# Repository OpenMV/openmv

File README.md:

# The Open-Source Machine Vision Project
  - [Overview](#overview)
  - [TensorFlow support](#tensorflow-support)
  - [Interface library](#interface-library)
    + [Note on serial port](#note-on-serial-port)
  - [ Building the firmware from source](#building-the-firmware-from-source)
  - [Contributing to the project](#contributing-to-the-project)
    + [Contribution guidelines](#contribution-guidelines)
    
## Overview

The OpenMV project brings machine vision to beginners with a user-friendly, open-source platform. OpenMV cameras are programmable in Python3 and feature advanced AI capabilities, including support for TensorFlow, ST Edge AI, and NPU acceleration through ARM Ethos-U55 and ST Neural-ART. The firmware includes a rich image image processing library, such as image filtering, feature detection, color tracking, QR and barcode decoding, AprilTag recognition, GIF and MJPEG recording and streaming, and much more.

The latest generation of OpenMV cameras includes the N6 and AE3 models. The OpenMV-N6 is powered by the STM32N6 microcontroller, which features a 1GHz/600 GOPS NPU, hardware H.264 encoding, high-speed USB, ISP, GPU, and a high-speed μSD card slot. It also comes equipped with WiFi/BLE, Gigabit Ethernet, and extensive GPIO pins—combining the power of a single-board computer with the flexibility of a microcontroller.

The OpenMV-AE3 is our smallest and most energy-efficient camera yet powered by the Alif Ensemble E3, with dual-core processors and dual Ethos-U55 NPUs. This ultra-low-power device can run YOLO models at 30 FPS while drawing only 0.25 W, and it consumes just 2.5 mW in deep sleep mode. It features a 1MP high-frame-rate color global shutter camera, an IMU, a microphone, an 8×8 distance sensor, and connectivity options such as high-speed USB, WiFi/BLE, and QWIIC—making it ideal for battery-powered AI vision applications.

Complementing the firmware is an intuitive, cross-platform IDE based on Qt Creator, specifically designed for machine vision development. The IDE lets users view the camera’s frame buffer in real time, adjust sensor settings, and run scripts directly on the device. It also provides a range of tools for image analysis, including tag generation, threshold definition, keypoint detection, and other processing functions.

The OpenMV project was successfully funded on Kickstarter in 2015 and has evolved significantly since its inception. For more information, visit [https://openmv.io](https://openmv.io).

## Interface library

The OpenMV Cam comes built-in with an RPC (Remote Python/Procedure Call) library which makes it easy to connect the OpenMV Cam to another microcontroller like the Arduino or ESP8266/32. The RPC Interface Library works over:

* Async Serial (UART) - at up **7.5 Mb/s** on the OpenMV Cam H7.
* I2C Bus - at up to **1 Mb/s** on the OpenMV Cam H7.
  * Using 1K pull up resistors.
* SPI Bus - at up to **20 Mb/s** on the OpenMV Cam H7.
  * Up to **80 Mb/s** or **40 Mb/s** is achievable with short enough wires.
* CAN Bus - at up to **1 Mb/s** on the OpenMV Cam H7.

With the RPC Library you can easily get image processing results, stream RAW or JPG image data, or have the OpenMV Cam control another Microcontroller for lower-level hardware control like driving motors.

You can find examples that run on the OpenMV Cam under `File->Examples->Remote Control` in OpenMV IDE and online [here](scripts/examples/34-Remote-Control). Finally, OpenMV provides the following libraries for interfacing your OpenMV Cam to other systems below:

* [Arduino Interface Library for CAN, I2C, SPI, UART Comms](https://github.com/openmv/openmv-arduino-rpc)
  * Works on all Arduino variants.
  * CAN support via the MCP2515 over SPI or via the CAN peripheral on the ESP32.

#### Note on serial port

If you only need to read `print()` output from a script running on an OpenMV camera over USB, then you only need to open the OpenMV camera Virtual COM Port and read lines of text from the serial port. For example (using [pyserial](https://pythonhosted.org/pyserial/index.html)):

```Python
import serial
ser = serial.Serial("COM3", timeout=1, dsrdtr=False)
while True:
    line = ser.readline().strip()
    if line: print(line)
```
The above code works for Windows, Mac, or Linux. You just need to change the above port name to the same name of the USB VCP port the OpenMV Cam shows up as (it will be under `/dev/` on Mac or Linux). Note that if you are opening the USB VCP port using another serial library and/or language make sure to set the DTR line to false - otherwise the OpenMV Cam will suppress printed output.

## Building the firmware from source

The easiest way to patch the firmware and rebuild it, is to fork this repository, enable Actions (from the Actions tab) in the forked repository, and pushing the changes. Our GitHub workflow rebuilds the firmware on pushes to the master branch and/or merging pull requests and generates a development release with attached separate firmware packages per supported board. For more complex changes, and building the OpenMV firmware from source locally, see [Building the Firmware From Source](https://github.com/openmv/openmv/blob/master/docs/firmware.md).

For more information about customizing your OpenMV Cam's configuration see [Board Configuration](docs/boards.md).

### Unix Port for Development

The Unix port runs OpenMV image processing without camera hardware. See the [Unix port guide](docs/unix-port.md) for the Linux Docker build, supported API and tests.

## Contributing to the project

Contributions are most welcome. If you are interested in contributing to the project, start by creating a fork of each of the following repositories:

* https://github.com/openmv/openmv.git
* https://github.com/openmv/micropython.git

Clone the forked openmv repository, and add a remote to the main openmv repository:
```bash
git clone --recursive https://github.com/<username>/openmv.git
git -C openmv remote add upstream https://github.com/openmv/openmv.git
```

Set the `origin` remote of the micropython submodule to the forked micropython repo:
```bash
git -C openmv/src/micropython remote set-url origin https://github.com/<username>/micropython.git
```

Finally add a remote to openmv's micropython fork:
```bash
git -C openmv/src/micropython remote add upstream https://github.com/openmv/micropython.git
```

Now the repositories are ready for pull requests. To send a pull request, create a new feature branch and push it to origin, and use Github to create the pull request from the forked repository to the upstream openmv/micropython repository. For example:
```bash
git checkout -b <some_branch_name>
<commit changes>
git push origin -u <some_branch_name>
```

### Contribution guidelines
Please follow the [best practices](https://developers.google.com/blockly/guides/modify/contribute/write_a_good_pr) when sending pull requests upstream. In general, the pull request should:
* Fix one problem. Don't try to tackle multiple issues at once.
* Split the changes into logical groups using git commits.
* Pull request title should be less than 78 characters, and match this pattern:
  * `<scope>:<1 space><description><.>`
* Commit subject line should be less than 78 characters, and match this pattern:
  * `<scope>:<1 space><description><.>`

Example PR titles or commit subject lines:
```
github: Update workflows.
Libtf: Add support for built-in models.
RPC library: Remove CAN bit timing function.
OPENMV4: Add readme template file.
ports/stm32/main.c: Fix storage label.
```

### Licensing

Most of the code in the repository is licensed under the MIT license, with the following exceptions:

* Some image library code is licensed under the GPL. This includes AGAST, LSD, and ZBAR. GPL code can be completely disabled in a build by defining `OMV_NO_GPL` in the `imlib_config.h` files.
* Third-party libraries and drivers in `lib` and `drivers` are licensed under various permissive licenses. Please consult the LICENSE file in each driver/library subdirectory for more details.
* Some drivers, modules, and libraries in OpenMV are proprietary and available for non-commercial use only. These proprietary components can be disabled during the build process. Official OpenMV hardware and licensed devices may use the proprietary code. For commercial licensing options, contact openmv@openmv.io.

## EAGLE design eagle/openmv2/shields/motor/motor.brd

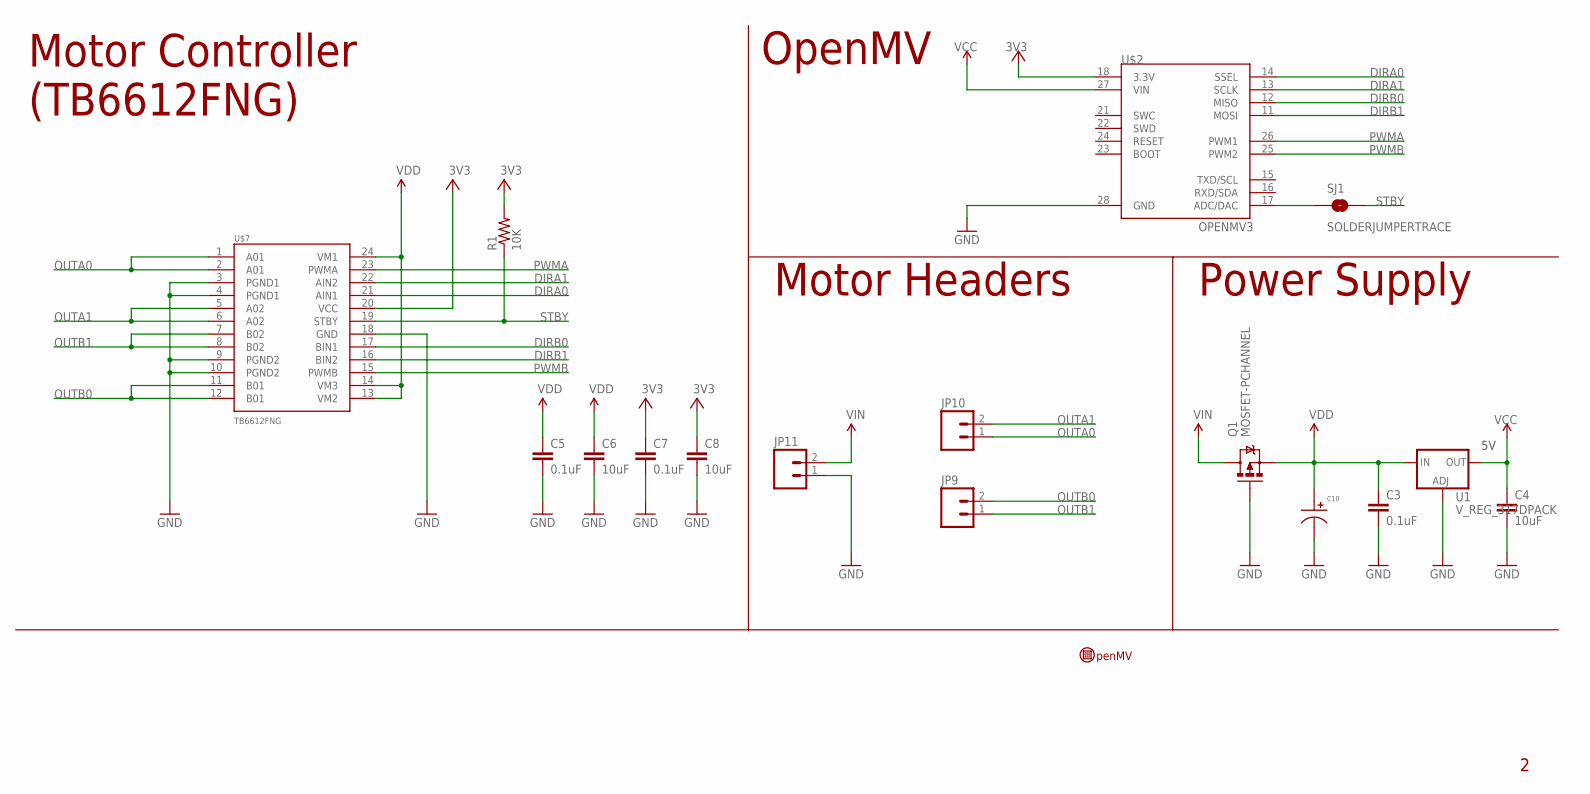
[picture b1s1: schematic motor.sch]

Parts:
C3, C5, C7: 0.1uF; 0603-CAP
C4, C6, C8: 10uF; 0805
C10: CAPACITOR_P_10MM; CP10MM
JP9, JP10, JP11: M023.5MM; SCREWTERMINAL-3.5MM-2
Q1: MOSFET-PCHANNEL; SOT23-3
R1: 10K; 0603-RES
SJ1: SOLDERJUMPERTRACE; SJ_2S-TRACE
U1: V_REG_317DPACK; V-REG_DPACK
U$2: OPENMV3
U$7: TB6612FNG; SSOP24
U$9: OPENMV-LOGO

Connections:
3V3: C7.1, C8.1, R1.2, U$2.18 (3.3V), U$7.20 (VCC)
DIRA0: U$2.14 (SSEL), U$7.21 (AIN1)
DIRA1: U$2.13 (SCLK), U$7.22 (AIN2)
DIRB0: U$2.12 (MISO), U$7.17 (BIN1)
DIRB1: U$2.11 (MOSI), U$7.16 (BIN2)
GND: C3.2, C4.2, C5.2, C6.2, C7.2, C8.2, C10.P$2, JP11.1, Q1.1 (G), U1.1 (ADJ), U$2.28 (GND), U$7.3 (PGND1), U$7.4 (PGND1), U$7.9 (PGND2), U$7.10 (PGND2), U$7.18 (GND)
OUTA0: JP10.1, U$7.1 (A01), U$7.2 (A01)
OUTA1: JP10.2, U$7.5 (A02), U$7.6 (A02)
OUTB0: JP9.2, U$7.11 (B01), U$7.12 (B01)
OUTB1: JP9.1, U$7.7 (B02), U$7.8 (B02)
PWMA: U$2.26 (PWM1), U$7.23 (PWMA)
PWMB: U$2.25 (PWM2), U$7.15 (PWMB)
STBY: R1.1, SJ1.2, U$7.19 (STBY)
STBY_TRACE: SJ1.1, U$2.17 (ADC/DAC)
VCC: C4.1, U1.4 (OUT), U$2.27 (VIN)
VDD: C3.1, C5.1, C6.1, C10.P$1, Q1.2 (S), U1.3 (IN), U$7.13 (VM2), U$7.14 (VM3), U$7.24 (VM1)
VIN: JP11.2, Q1.3 (D)

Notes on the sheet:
Motor Controller (TB6612FNG)
Motor Headers
OpenMV
Power Supply

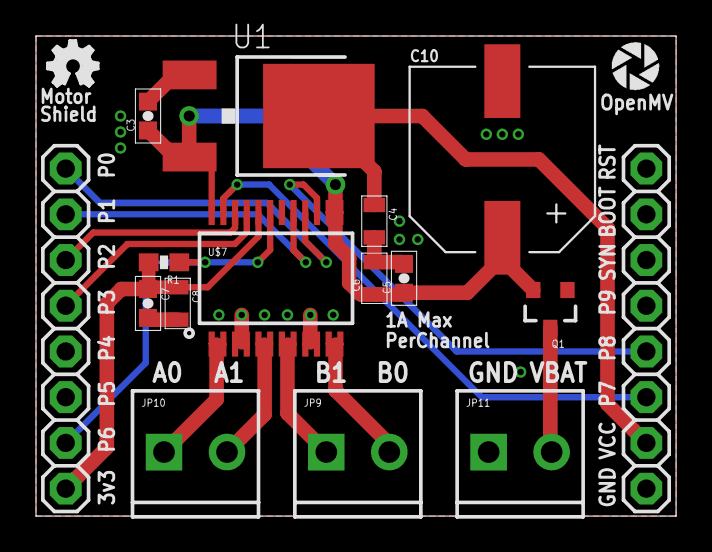
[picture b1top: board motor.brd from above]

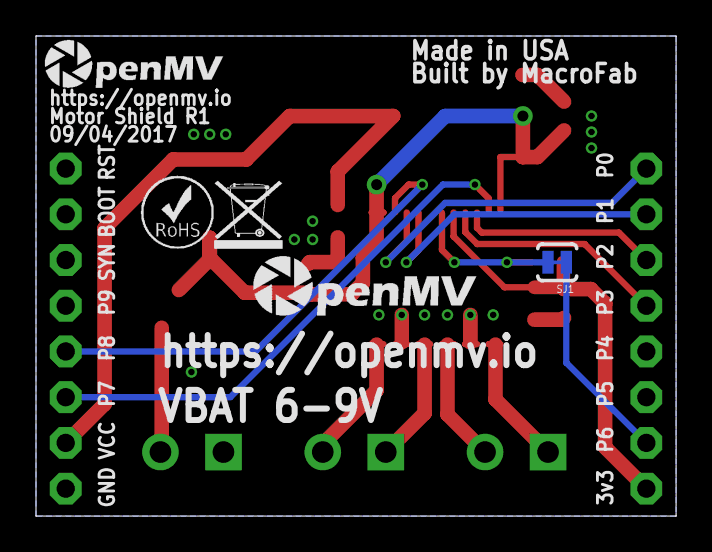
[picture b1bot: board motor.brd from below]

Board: 2 copper layers, 35.6 x 26.7 mm, 22 parts (5 on the bottom side), 17 nets.

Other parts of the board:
U$3: OMV-LOGO
U$5: ROHS
U$6: WEEE
U$10: OMV-LOGO-SMALL
U$11: OSHW_FILLX100_NOTEXT

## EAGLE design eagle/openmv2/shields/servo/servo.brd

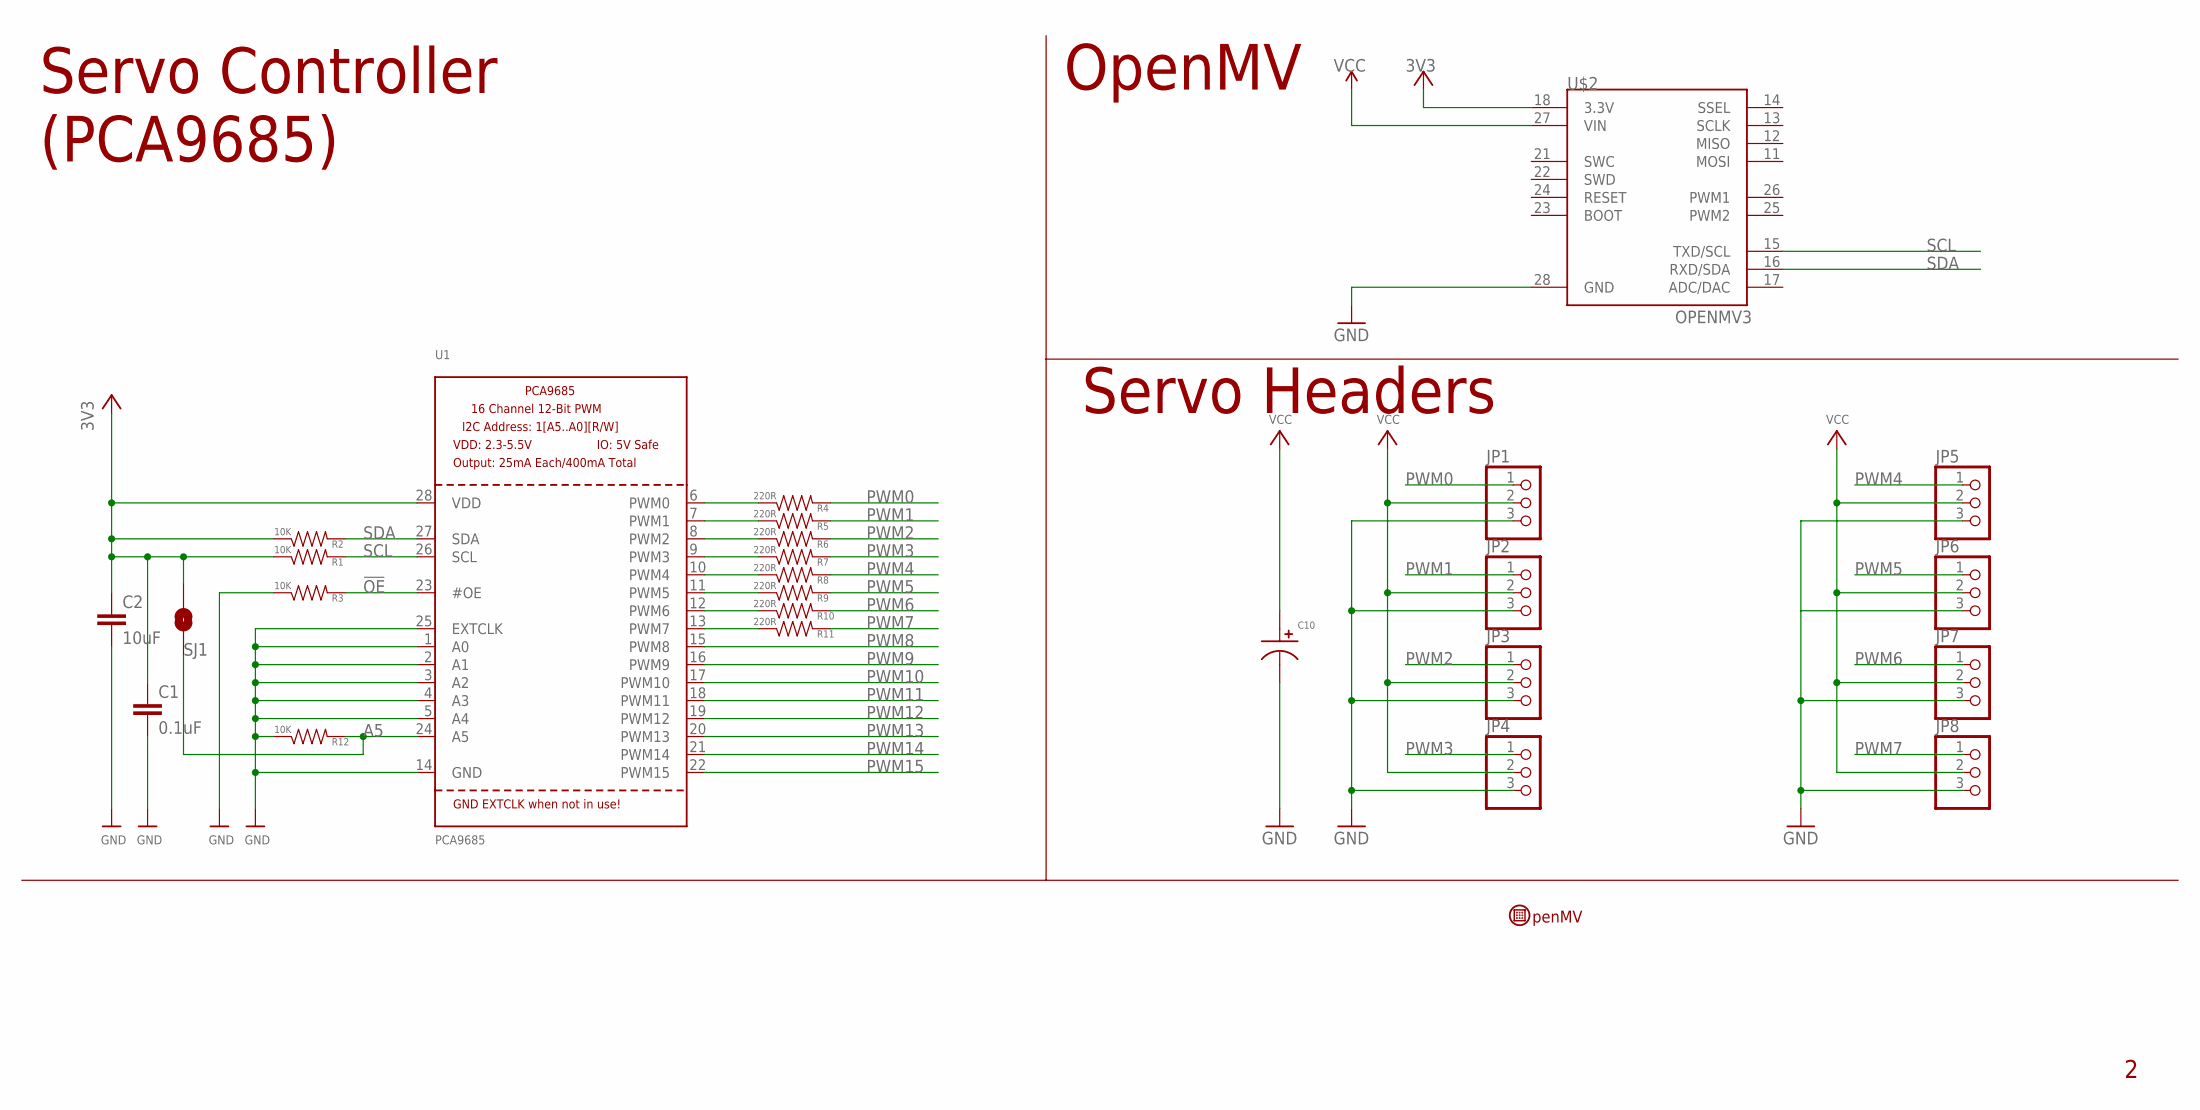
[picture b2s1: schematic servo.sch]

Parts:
C1: 0.1uF; 0603-CAP
C2: 10uF; 0805
C10: CAPACITOR_P_10MM; CP10MM
JP1, JP2, JP3, JP4, JP5, JP6, JP7, JP8: PINHD-1X3; 1X03
R1, R2, R3, R12: 10K; 0603-RES
R4, R5, R6, R7, R8, R9, R10, R11: 220R; 0603-RES
SJ1: SOLDERJUMPERNO; SJ_2S-NO
U1: PCA9685; TSSOP28
U$2: OPENMV3
U$9: OPENMV-LOGO

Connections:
3V3: C1.1, C2.1, R1.1, R2.1, SJ1.2, U1.28 (VDD), U$2.18 (3.3V)
!OE: R3.2, U1.23 (#OE)
A5: R12.2, SJ1.1, U1.24 (A5)
C3: R11.1, U1.13 (PWM7)
GND: C1.2, C2.2, C10.P$2, JP1.3, JP2.3, JP3.3, JP4.3, JP5.3, JP6.3, JP7.3, JP8.3, R3.1, R12.1, U1.1 (A0), U1.2 (A1), U1.3 (A2), U1.4 (A3), U1.5 (A4), U1.14 (GND), U1.25 (EXTCLK), U$2.28 (GND)
unnamed: R4.1, U1.6 (PWM0)
unnamed: R5.1, U1.7 (PWM1)
unnamed: R6.1, U1.8 (PWM2)
unnamed: R7.1, U1.9 (PWM3)
unnamed: R8.1, U1.10 (PWM4)
unnamed: R9.1, U1.11 (PWM5)
unnamed: R10.1, U1.12 (PWM6)
PWM0: JP1.1, R4.2
PWM1: JP2.1, R5.2
PWM2: JP3.1, R6.2
PWM3: JP4.1, R7.2
PWM4: JP5.1, R8.2
PWM5: JP6.1, R9.2
PWM6: JP7.1, R10.2
PWM7: JP8.1, R11.2
PWM8: U1.15 (PWM8)
PWM9: U1.16 (PWM9)
PWM10: U1.17 (PWM10)
PWM11: U1.18 (PWM11)
PWM12: U1.19 (PWM12)
PWM13: U1.20 (PWM13)
PWM14: U1.21 (PWM14)
PWM15: U1.22 (PWM15)
SCL: R1.2, U1.26 (SCL), U$2.15 (TXD/SCL)
SDA: R2.2, U1.27 (SDA), U$2.16 (RXD/SDA)
VCC: C10.P$1, JP1.2, JP2.2, JP3.2, JP4.2, JP5.2, JP6.2, JP7.2, JP8.2, U$2.27 (VIN)

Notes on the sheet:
Servo Controller (PCA9685)
Servo Headers
OpenMV

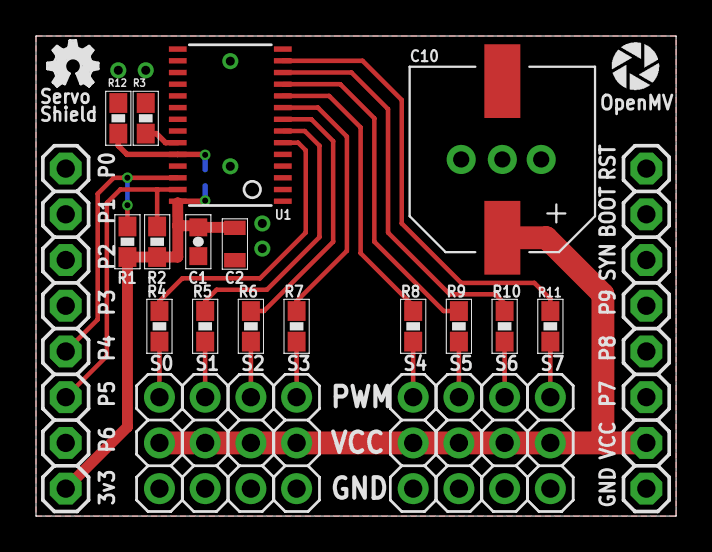
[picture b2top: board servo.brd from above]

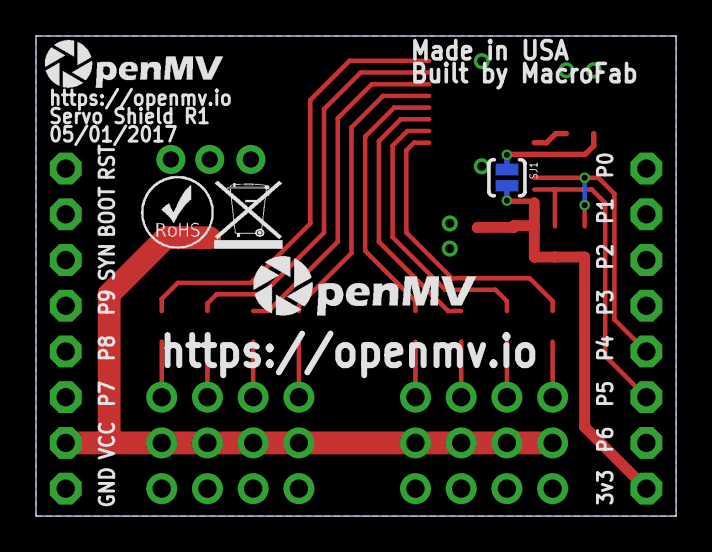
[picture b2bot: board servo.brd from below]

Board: 2 copper layers, 35.6 x 26.7 mm, 32 parts (5 on the bottom side), 23 nets.

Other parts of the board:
U$3: OMV-LOGO
U$5: ROHS
U$6: WEEE
U$10: OMV-LOGO-SMALL
U$11: OSHW_FILLX100_NOTEXT

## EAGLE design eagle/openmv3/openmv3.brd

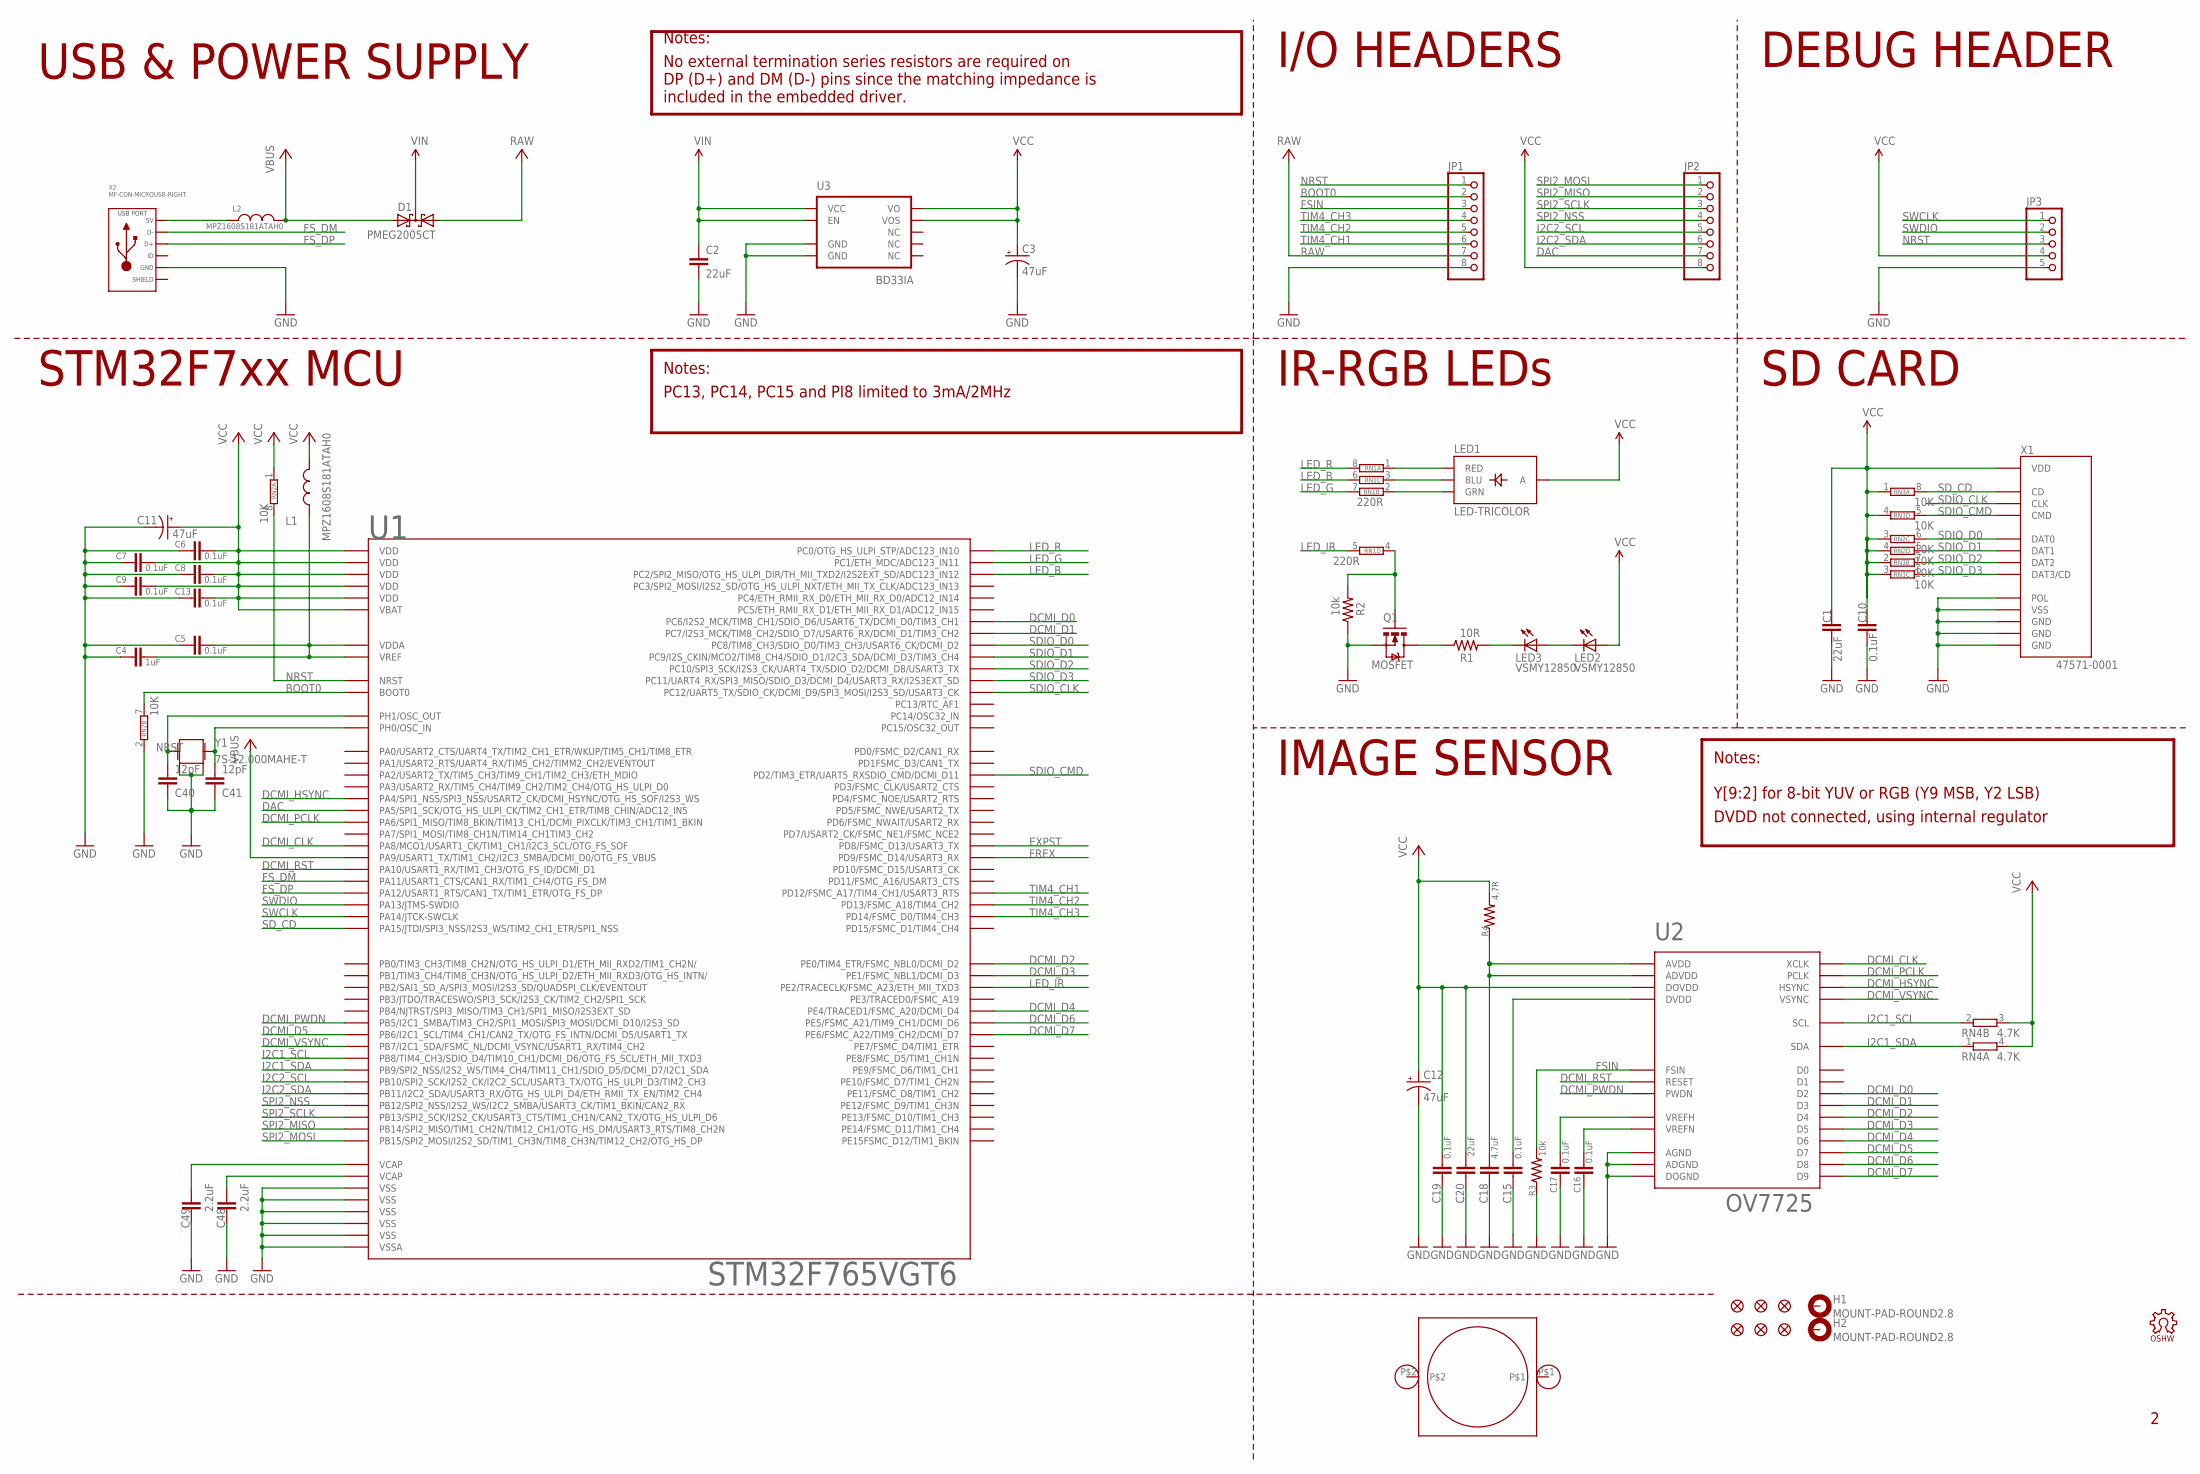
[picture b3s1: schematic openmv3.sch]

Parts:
C1, C2, C20: 22uF; 0805
C3, C11, C12: 47uF; EIA3216
C4: 1uF; 0603-CAP
C5, C6, C7, C8, C9, C10, C13, C15, C16, C17, C19: 0.1uF; 0603-CAP
C18: 4.7uF; 0603-CAP
C40, C41: 12pF; 0603-CAP
C48, C49: 2.2uF; 0603-CAP
D1: PMEG2005CT; SOT23
F1, F2, F3, F4, F5, F6: FIDUCIAL1X2; FIDUCIAL-1X2
H1, H2: MOUNT-PAD-ROUND2.8; 2,8-PAD
JP1, JP2: PINHD-1X8; 1X08
JP3: PINHD-1X5; 1X05
L1, L2: MPZ1608S181ATAH0; 0603
LED1: LED-TRICOLOR; LED-TRICOLOR-SMD-MF
LED2, LED3: VSMY12850; LED-1206
LM1: LENSMOUNT20MM; LENSMOUNT-20MM
LOGO1: OSHW_LOGO_FILLX0100-NT; OSHW_FILLX100_NOTEXT
Q1: MOSFET; SOT23-3
R1: 10R; 0603-RES
R2, R3: 10k; 0603-RES
R4: 4.7R; 0603-RES
RN1: 220R; EXBV8V
RN2, RN3: 10K; EXBV8V
RN4: 4.7K; EXBV4V
U1: STM32F765VGT6; LQFP100
U2: OV7725; CSP2-28
U3: BD33IA; HTSOP-J8
X1: 47571-0001; USD-47571
X2: MF-CON-MICROUSB-RIGHT; MICROUSB-RIGHT
Y1: 7S-12.000MAHE-T; CRYSTAL-2.5X2.0

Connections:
BOOT0: JP1.2, RN2.7 (2), U1.94 (BOOT0)
DAC: JP2.7, U1.29 (PA5/SPI1_SCK/OTG_HS_ULPI_CK/TIM2_CH1_ET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)
DCMI_CLK: U1.67 (PA8/MCO1/USART1_CK/TIM1_CH1/I2C3_SCL/OT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), U2.F3 (XCLK)
DCMI_D0: U1.63 (PC6/I2S2_MCK/TIM8_CH1/SDIO_D6/USART6_TX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), U2.F5 (D2)
DCMI_D1: U1.64 (PC7/I2S3_MCK/TIM8_CH2/SDIO_D7/USART6_RX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), U2.F2 (D3)
DCMI_D2: U1.97 (PE0/TIM4_ETR/FSMC_NBL0/DCMI_D2), U2.D6 (D4)
DCMI_D3: U1.98 (PE1/FSMC_NBL1/DCMI_D3), U2.D1 (D5)
DCMI_D4: U1.3 (PE4/TRACED1/FSMC_A20/DCMI_D4), U2.E6 (D6)
DCMI_D5: U1.92 (PB6/I2C1_SCL/TIM4_CH1/CAN2_TX/OTG_FS_IN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), U2.E1 (D7)
DCMI_D6: U1.4 (PE5/FSMC_A21/TIM9_CH1/DCMI_D6), U2.F6 (D8)
DCMI_D7: U1.5 (PE6/FSMC_A22/TIM9_CH2/DCMI_D7), U2.F1 (D9)
DCMI_HSYNC: U1.28 (PA4/SPI1_NSS/SPI3_NSS/USART2_CK/DCMI_HS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), U2.B6 (HSYNC)
DCMI_PCLK: U1.30 (PA6/SPI1_MISO/TIM8_BKIN/TIM13_CH1/DCMI_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), U2.E4 (PCLK)
DCMI_PWDN: U1.91 (PB5/I2C1_SMBA/TIM3_CH2/SPI1_MOSI/SPI3_M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), U2.C1 (PWDN)
DCMI_RST: U1.69 (PA10/USART1_RX/TIM1_CH3/OTG_FS_ID/DCMI_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), U2.A2 (RESET)
DCMI_VSYNC: U1.93 (PB7/I2C1_SDA/FSMC_NL/DCMI_VSYNC/USART1_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), U2.C6 (VSYNC)
EXPST: U1.55 (PD8/FSMC_D13/USART3_TX)
FREX: U1.56 (PD9/FSMC_D14/USART3_RX)
FSIN: JP1.3, R3.2, U2.A4 (FSIN)
FS_DM: U1.70 (PA11/USART1_CTS/CAN1_RX/TIM1_CH4/OTG_FS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), X2.2 (D-)
FS_DP: U1.71 (PA12/USART1_RTS/CAN1_TX/TIM1_ETR/OTG_FS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), X2.3 (D+)
GND: C1.2, C2.2, C3.C (-), C4.2, C5.2, C6.2, C7.2, C8.2, C9.2, C10.2, C11.C (-), C12.C (-), C13.2, C15.2, C16.2, C17.2, C18.2, C19.2, C20.2, C40.1, C41.1, C48.2, C49.2, JP1.8, JP3.5, Q1.2 (S), R2.1, R3.1, RN2.2 (1), U1.10 (VSS), U1.19 (VSSA), U1.26 (VSS), U1.49 (VSS), U1.74 (VSS), U1.99 (VSS), U2.B1 (ADGND), U2.B4 (AGND), U2.F4 (DOGND), U3.3 (GND), U3.P$1 (GND), X1.G$1 (GND), X1.G$2 (GND), X1.G$3 (GND), X1.G$4 (POL), X1.P$6 (VSS), X2.5 (GND), Y1.2, Y1.4
I2C1_SCL: RN4.2 (1), U1.95 (PB8/TIM4_CH3/SDIO_D4/TIM10_CH1/DCMI_D6/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), U2.A5 (SCL)
I2C1_SDA: RN4.1, U1.96 (PB9/SPI2_NSS/I2S2_WS/TIM4_CH4/TIM11_CH1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), U2.B5 (SDA)
I2C2_SCL: JP2.5, U1.46 (PB10/SPI2_SCK/I2S2_CK/I2C2_SCL/USART3_T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)
I2C2_SDA: JP2.6, U1.47 (PB11/I2C2_SDA/USART3_RX/OTG_HS_ULPI_D4/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)
LED_B: RN1.6 (2), U1.17 (PC2/SPI2_MISO/OTG_HS_ULPI_DIR/TH_MII_TX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)
LED_G: RN1.7 (2), U1.16 (PC1/ETH_MDC/ADC123_IN11)
LED_IR: RN1.5 (2), U1.1 (PE2/TRACECLK/FSMC_A23/ETH_MII_TXD3)
LED_R: RN1.8 (2), U1.15 (PC0/OTG_HS_ULPI_STP/ADC123_IN10)
unnamed: C17.1, U2.A3 (VREFH)
unnamed: C40.2, U1.13 (PH1/OSC_OUT), Y1.3 (2)
unnamed: C16.1, U2.B2 (VREFN)
unnamed: C41.2, U1.12 (PH0/OSC_IN), Y1.1
unnamed: Q1.1 (G), R2.2, RN1.4 (1)
unnamed: LED1.B (BLU), RN1.3 (1)
unnamed: L2.1, X2.1 (5V)
unnamed: LED1.R (RED), RN1.1
unnamed: LED1.G (GRN), RN1.2 (1)
unnamed: LED3.C, R1.2
unnamed: C4.1, C5.1, L1.1, U1.20 (VREF), U1.21 (VDDA)
unnamed: C18.1, R4.1, U2.A1 (ADVDD), U2.B3 (AVDD)
unnamed: Q1.3 (D), R1.1
unnamed: C15.1, U2.E3 (DVDD)
unnamed: LED2.C, LED3.A
NRST: JP1.1, JP3.3, RN2.8 (2), U1.14 (NRST)
RAW: D1.1 (A1), JP1.7
SDIO_CLK: U1.80 (PC12/UART5_TX/SDIO_CK/DCMI_D9/SPI3_MOSI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), X1.P$5 (CLK)
SDIO_CMD: RN3.5 (2), U1.83 (PD2/TIM3_ETR/UART5_RXSDIO_CMD/DCMI_D11), X1.P$3 (CMD)
SDIO_D0: RN2.6 (2), U1.65 (PC8/TIM8_CH3/SDIO_D0/TIM3_CH3/USART6_CK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), X1.P$7 (DAT0)
SDIO_D1: RN2.5 (2), U1.66 (PC9/I2S_CKIN/MCO2/TIM8_CH4/SDIO_D1/I2C3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), X1.P$8 (DAT1)
SDIO_D2: RN3.7 (2), U1.78 (PC10/SPI3_SCK/I2S3_CK/UART4_TX/SDIO_D2/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), X1.P$1 (DAT2)
SDIO_D3: RN3.6 (2), U1.79 (PC11/UART4_RX/SPI3_MISO/SDIO_D3/DCMI_D4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), X1.P$2 (DAT3/CD)
SD_CD: RN3.8 (2), U1.77 (PA15/JTDI/SPI3_NSS/I2S3_WS/TIM2_CH1_ETR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), X1.G$5 (CD)
SPI2_MISO: JP2.2, U1.53 (PB14/SPI2_MISO/TIM1_CH2N/TIM12_CH1/OTG_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)
SPI2_MOSI: JP2.1, U1.54 (PB15/SPI2_MOSI/I2S2_SD/TIM1_CH3N/TIM8_C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)
SPI2_NSS: JP2.4, U1.51 (PB12/SPI2_NSS/I2S2_WS/I2C2_SMBA/USART3_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)
SPI2_SCLK: JP2.3, U1.52 (PB13/SPI2_SCK/I2S2_CK/USART3_CTS/TIM1_C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)
SWCLK: JP3.1, U1.76 (PA14/JTCK-SWCLK)
SWDIO: JP3.2, U1.72 (PA13/JTMS-SWDIO)
TIM4_CH1: JP1.6, U1.59 (PD12/FSMC_A17/TIM4_CH1/USART3_RTS)
TIM4_CH2: JP1.5, U1.60 (PD13/FSMC_A18/TIM4_CH2)
TIM4_CH3: JP1.4, U1.61 (PD14/FSMC_D0/TIM4_CH3)
VBUS: D1.2 (A2), L2.2, U1.68 (PA9/USART1_TX/TIM1_CH2/I2C3_SMBA/DCMI_D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)
VCAP1: C49.1, U1.48 (VCAP)
VCAP2: C48.1, U1.73 (VCAP)
VCC: C1.1, C3.A (+), C6.1, C7.1, C8.1, C9.1, C10.1, C11.A (+), C12.A (+), C13.1, C19.1, C20.1, JP2.8, JP3.4, L1.2, LED1.A, LED2.A, R4.2, RN2.1, RN2.3 (1), RN2.4 (1), RN3.1, RN3.2 (1), RN3.3 (1), RN3.4 (1), RN4.3 (2), RN4.4 (2), U1.6 (VBAT), U1.11 (VDD), U1.27 (VDD), U1.50 (VDD), U1.75 (VDD), U1.100 (VDD), U2.E5 (DOVDD), U3.1 (VO), U3.2 (VOS), X1.P$4 (VDD)
VIN: C2.1, D1.3 (CC), U3.5 (EN), U3.8 (VCC)

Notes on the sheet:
PC13, PC14, PC15 and PI8 limited to 3mA/2MHz
SD CARD
Y[9:2] for 8-bit YUV or RGB (Y9 MSB, Y2 LSB)
DVDD not connected, using internal regulator
Notes:
IMAGE SENSOR
STM32F7xx MCU
IR-RGB LEDs
USB & POWER SUPPLY
DEBUG HEADER
I/O HEADERS
No external termination series resistors are required on DP (D+) and DM (D-) pins since the matching impedance is included in the embedded driver.

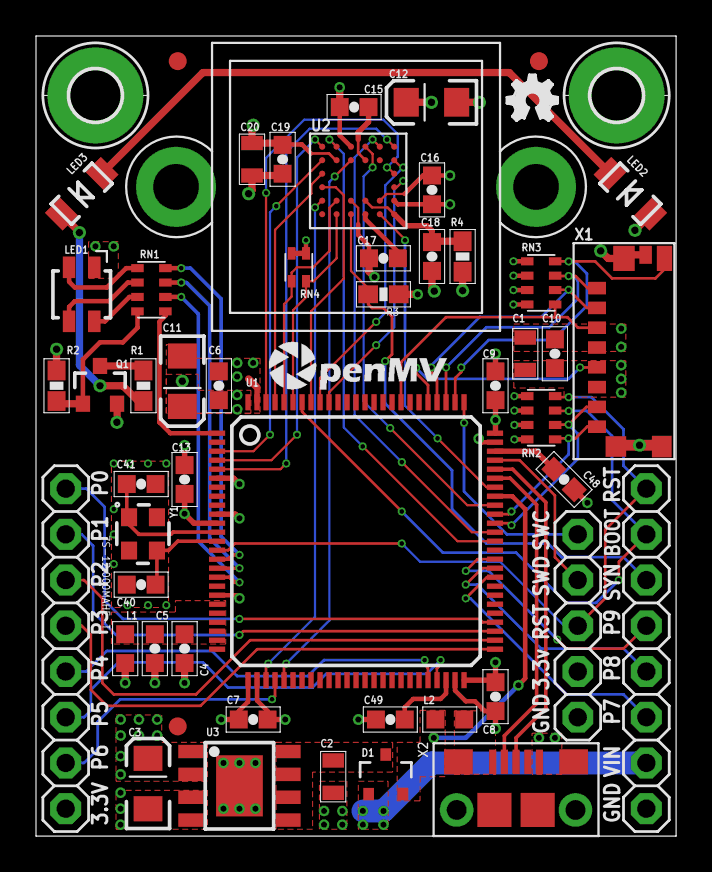
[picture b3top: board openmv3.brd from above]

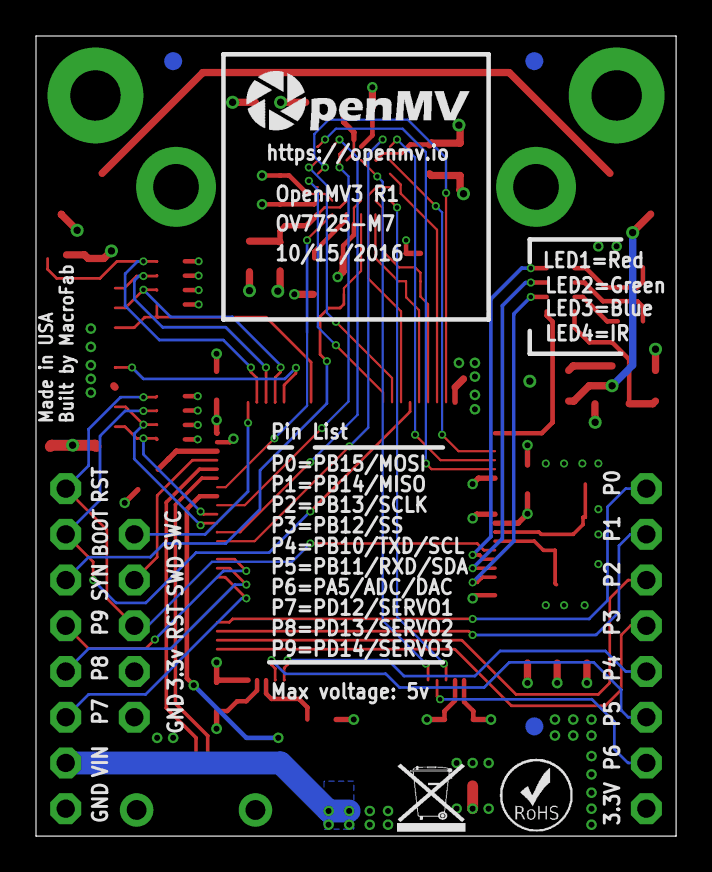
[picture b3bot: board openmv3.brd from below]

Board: 4 copper layers, 35.6 x 44.5 mm, 61 parts (6 on the bottom side), 66 nets.

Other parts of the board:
U$1: WEEE
U$2: ROHS
U$3: OMV-LOGO
U$4: OMV-LOGO-SMALL

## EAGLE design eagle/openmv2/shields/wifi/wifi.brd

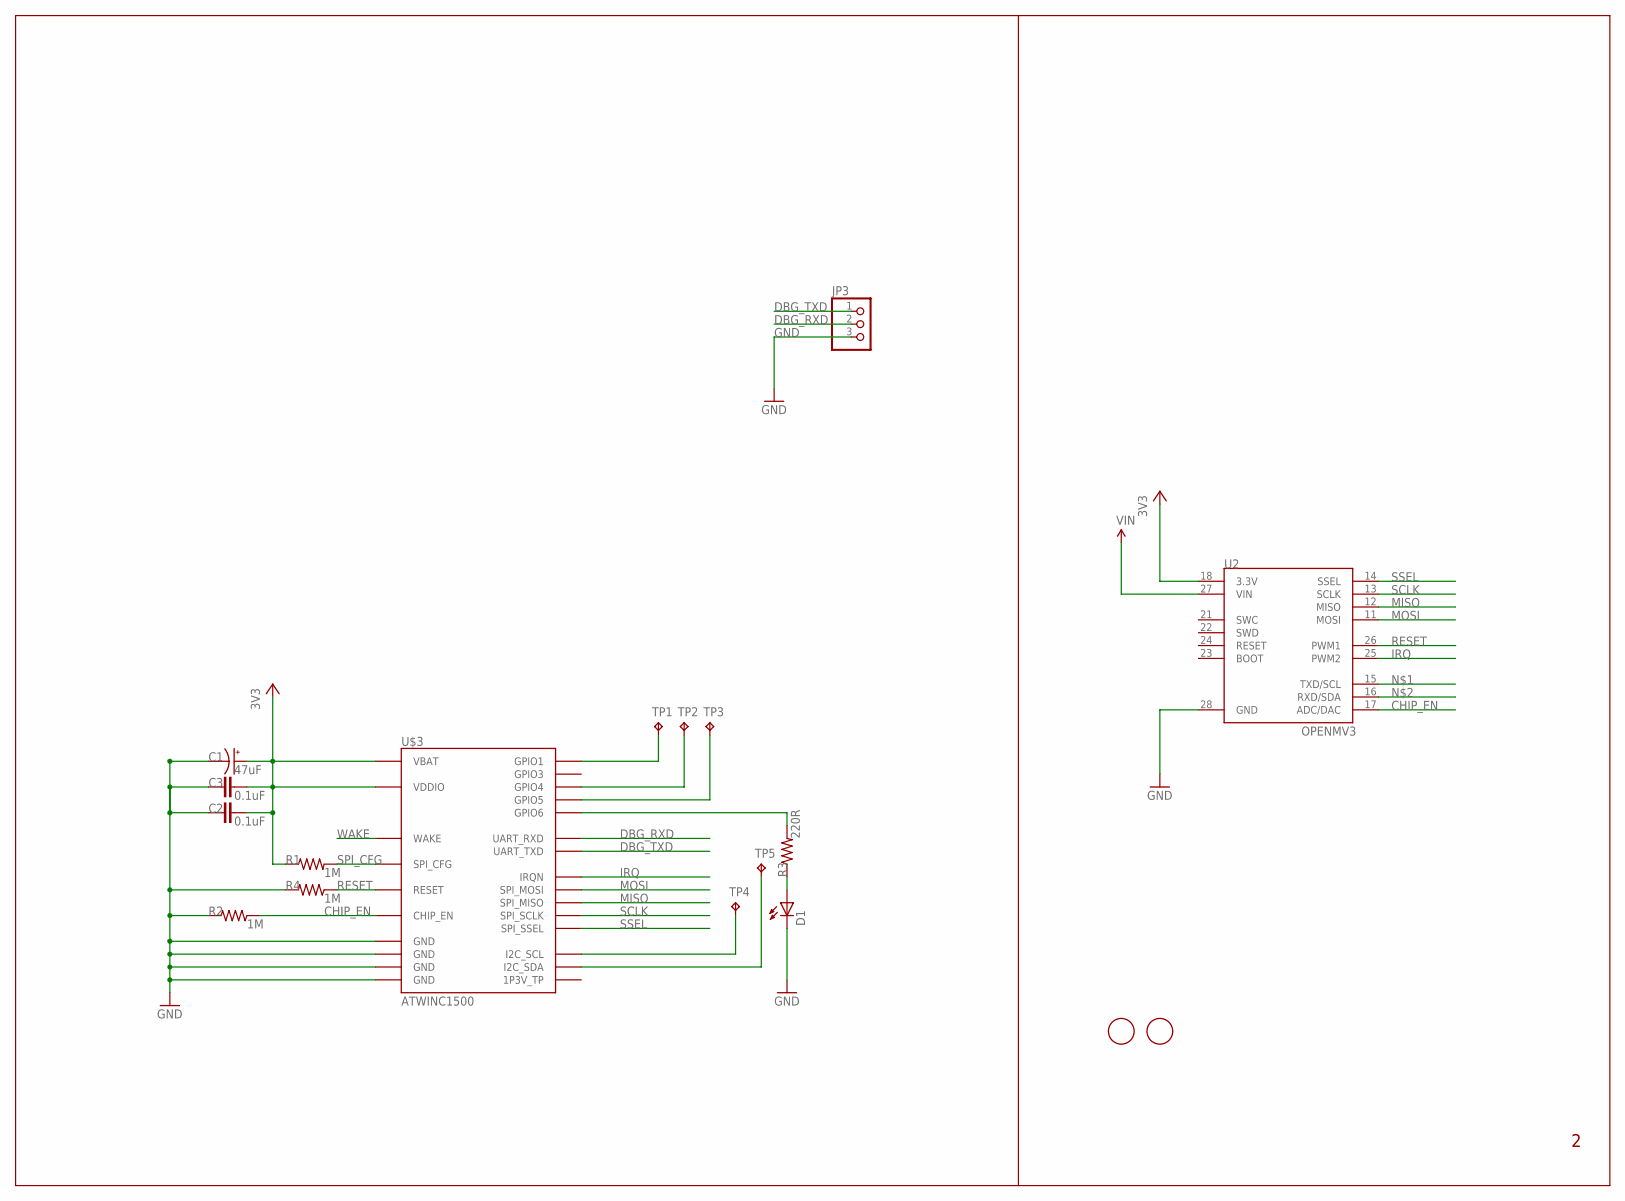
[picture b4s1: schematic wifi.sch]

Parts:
C1: 47uF; EIA3216
C2, C3: 0.1uF; 0603-CAP
D1: LED0603; LED-0603
JP3: PINHD-1X3; 1X03
R1, R2, R4: 1M; 0603-RES
R3: 220R; 0603-RES
TP1, TP4, TP5: TPTP12R; TP12R
TP2, TP3: TPTP11R; TP11R
U2: OPENMV3
U$1, U$2: FIDUCIAL; FIDUCIAL_1MM
U$3: ATWINC1500

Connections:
3V3: C1.A (+), C2.2, C3.2, R1.1, U2.18 (3.3V), U$3.P$20 (VBAT), U$3.P$23 (VDDIO)
CHIP_EN: R2.1, U2.17 (ADC/DAC), U$3.P$22 (CHIP_EN)
DBG_RXD: JP3.2, U$3.P$19 (UART_RXD)
DBG_TXD: JP3.1, U$3.P$14 (UART_TXD)
GND: C1.C (-), C2.1, C3.1, D1.C, JP3.3, R2.2, R4.2, U2.28 (GND), U$3.P$9 (GND), U$3.P$12 (GND), U$3.P$28 (GND), U$3.P$29 (GND)
IRQ: U2.25 (PWM2), U$3.P$13 (IRQN)
MISO: U2.12 (MISO), U$3.P$17 (SPI_MISO)
MOSI: U2.11 (MOSI), U$3.P$15 (SPI_MOSI)
unnamed: TP1.TP, U$3.P$21 (GPIO1)
unnamed: TP4.TP, U$3.P$2 (I2C_SCL)
unnamed: TP5.TP, U$3.P$3 (I2C_SDA)
unnamed: D1.A, R3.1
unnamed: TP2.TP, U$3.P$26 (GPIO4)
unnamed: TP3.TP, U$3.P$27 (GPIO5)
unnamed: R3.2, U$3.P$1 (GPIO6)
RESET: R4.1, U2.26 (PWM1), U$3.P$4 (RESET)
SCLK: U2.13 (SCLK), U$3.P$18 (SPI_SCLK)
SPI_CFG: R1.2, U$3.P$10 (SPI_CFG)
SSEL: U2.14 (SSEL), U$3.P$16 (SPI_SSEL)
VIN: U2.27 (VIN)
WAKE: U$3.P$11 (WAKE)

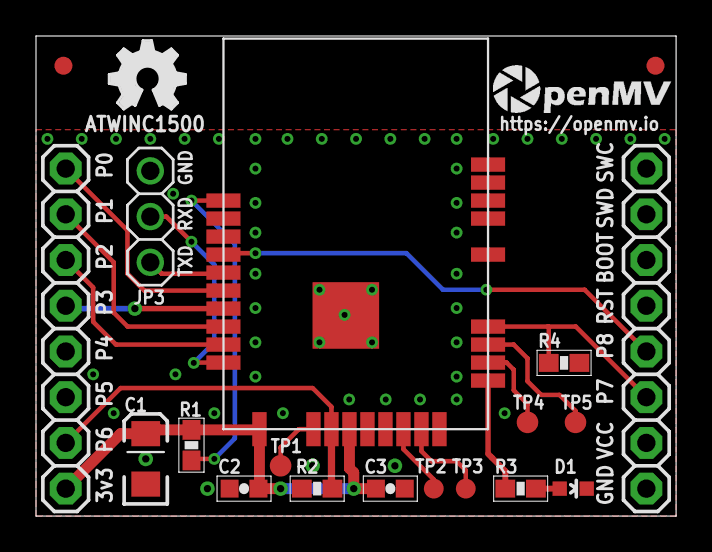
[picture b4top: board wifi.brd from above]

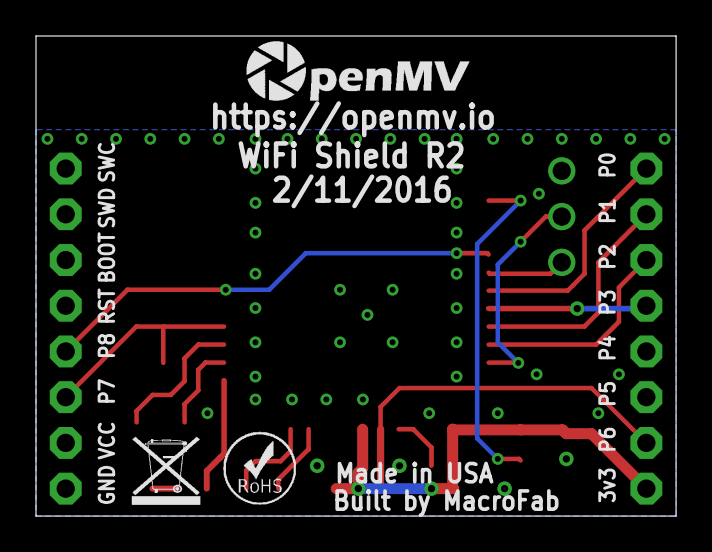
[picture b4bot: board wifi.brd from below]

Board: 2 copper layers, 35.6 x 26.7 mm, 23 parts (3 on the bottom side), 19 nets.

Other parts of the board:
U$4: OMV-LOGO
U$5: ROHS
U$6: WEEE
U$7: OSHW_FILLX150_NOTEXT
U$10: OMV-LOGO-SMALL

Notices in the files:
eagle/openmv2/openmv2.sch:
Copyright (c) 2013 Ibrahim Abd Elkader
This work is licensed under the Creative Commons Attribution-ShareAlike 3.0 License.
To view a copy of this license, visit http://creativecommons.org/licenses/by-sa/3.0
eagle/openmv2/shields/motor/motor.sch:
Copyright (c) 2017 OpenMV LLC
This work is licensed under the Creative Commons Attribution-ShareAlike 4.0 License.
To view a copy of this license, visit http://creativecommons.org/licenses/by-sa/4.0
